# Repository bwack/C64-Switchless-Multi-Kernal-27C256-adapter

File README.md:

[![Badge License]][License]

<br>

![Logo]

<br>

<div align = center>

***A C64 + Disk Drives Switch-less Multi*** <br>
***Kernel ROM Adapter / Switcher***

<br>

---

[![Button Playlist]][Playlist]   
[![Button OSHPark]][OSHPark]   
[![Button Forum]][Forum]

[![Button Usage]][Usage]  
[![Button Develop]][Develop]  
[![Button Changelog]][Changelog]

---

<br>
<br>

<br>

## Supported Devices

![C64]  ![C64C]  ![1541]  ![1541C]  ![1541-II] 

<br>

</div>
  
<br>

## Boards

### Long

The  `longboard`  is designed for <br>
the  <kbd> C64 </kbd>  **+**  <kbd> 1541 </kbd>  **/**  <kbd> 1541Late </kbd>

<br>

### Short

The  `shortboard`  is designed for <br>
the  <kbd> C64C </kbd>  **+**  <kbd> 1541C </kbd>  **/**  <kbd> 1541-II </kbd>

<br>

### Note

*The innards of  `C64`  /  `C64C`  and  `1541`  /  `1541C`* <br>
*are often mixed together, and you must check their* <br>
*cases to be sure which boards they have.*

<br>
<br>

## Acknowledgment

### Based On   [<kbd> Sven Petersen </kbd>][Petersen]

*[C64 Kernal Adaptor Switch Shortboard]*

### Old Version   [<kbd> DiscoHR </kbd>][DiscoHR]

*[C64C C128 Multikernal Adapter]*

*It is possible to reused the original LED / Cable assembly.*

### Idea From   [<kbd> Tebl </kbd>][DiscoHR]

*[C64 Kernal Switcher]*

<br>

<!----------------------------------------------------------------------------->

[Playlist]: https://www.youtube.com/playlist?list=PLtQOf_JULmrQTB7486X5pXG1Aaxbl_RdE
[OSHPark]: https://oshpark.com/profiles/bwack 'Order The Board'
[Forum]: http://www.lemon64.com/forum/viewtopic.php?p=747333 'Lemon64 Forum Post'

[Changelog]: Documentation/Changelog.md
[Develop]: Documentation/Develop.md
[License]: LICENSE
[Usage]: Documentation/Usage.md
[Logo]: User%20Guide/media/SKS64-Logos-Ver2.png

[Badge License]: https://img.shields.io/badge/Open_Hardware-1.2-292961?style=for-the-badge

<!--------------------------------{ Devices }---------------------------------->

[1541-II]: https://img.shields.io/badge/１５４１－ＩＩ-d7cdbb?style=flat
[1541C]: https://img.shields.io/badge/１５４１Ｃ-d7cdbb?style=flat
[1541]: https://img.shields.io/badge/１５４１-d7cdbb?style=flat
[C64C]: https://img.shields.io/badge/Ｃ６４Ｃ-d7cdbb?style=flat
[C64]: https://img.shields.io/badge/Ｃ６４-d7cdbb?style=flat

<!----------------------------{ Acknowledgment }------------------------------->

[C64 Kernal Adaptor Switch Shortboard]: https://github.com/svenpetersen1965/C64-Kernal-Adaptor-Switch-short-board-
[C64C C128 Multikernal Adapter]: https://github.com/discoHR/C64C-C128-multikernal-adapter
[C64 Kernal Switcher]: https://github.com/tebl/C64-Kernal-Switcher

[Petersen]: https://github.com/svenpetersen1965
[DiscoHR]: https://github.com/discoHR
[Tebl]: https://github.com/tebl

<!--------------------------------{ Buttons }---------------------------------->

[Button Changelog]: https://img.shields.io/badge/Changelog-19abdd?style=for-the-badge&logoColor=white&logo=AzureArtifacts
[Button Playlist]: https://img.shields.io/badge/Playlist-FF0000?style=for-the-badge&logoColor=white&logo=Youtube
[Button Develop]: https://img.shields.io/badge/Develop-00979D?style=for-the-badge&logoColor=white&logo=Arduino
[Button OSHPark]: https://img.shields.io/badge/OSHPark-752c8d?style=for-the-badge&logoColor=white&logo=Houzz
[Button Usage]: https://img.shields.io/badge/Usage-ED145B?style=for-the-badge&logoColor=white&logo=AppleArcade
[Button Forum]: https://img.shields.io/badge/Forum-5287B8?style=for-the-badge&logoColor=white&logo=AskUbuntu

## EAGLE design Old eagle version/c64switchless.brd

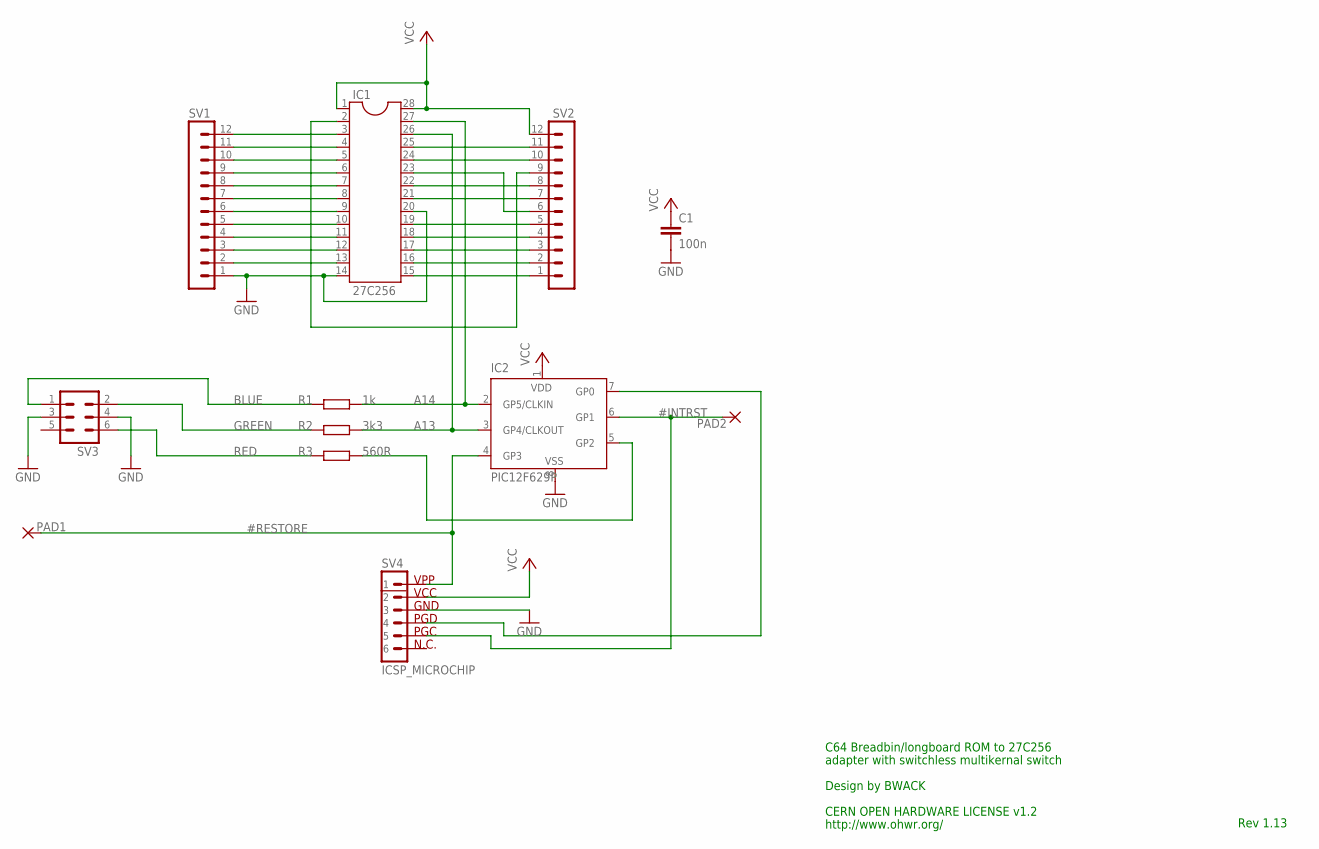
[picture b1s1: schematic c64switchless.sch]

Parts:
C1: 100n; C025-024X044
IC1: 27C256; DIL28SPECIAL
IC2: PIC12F629P; DIL8
PAD1, PAD2: WIREPAD1,6/0,9; 1,6/0,9
R1: 1k; 0207/10
R2: 3k3; 0207/10
R3: 560R; 0207/10
SV1, SV2: MA12-1ROUND
SV3: MA03-2
SV4: ICSP_MICROCHIP

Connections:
#INTRST: IC2.6 (GP1), PAD2.1, SV4.5
#RESTORE: IC2.4 (GP3), PAD1.1, SV4.1
A13: IC1.26, IC2.3 (GP4/CLKOUT), R2.2
A14: IC1.27, IC2.2 (GP5/CLKIN), R1.2
BLUE: R1.1, SV3.1
GND: C1.2, IC1.14, IC1.20, IC2.8 (VSS), SV1.1, SV3.3, SV3.4, SV4.3
GREEN: R2.1, SV3.2
unnamed: IC2.7 (GP0), SV4.4
unnamed: IC1.13, SV1.2
unnamed: IC1.12, SV1.3
unnamed: IC1.11, SV1.4
unnamed: IC1.10, SV1.5
unnamed: IC1.9, SV1.6
unnamed: IC1.8, SV1.7
unnamed: IC1.7, SV1.8
unnamed: IC1.6, SV1.9
unnamed: IC1.5, SV1.10
unnamed: IC1.4, SV1.11
unnamed: IC1.3, SV1.12
unnamed: IC1.15, SV2.1
unnamed: IC1.16, SV2.2
unnamed: IC1.17, SV2.3
unnamed: IC1.18, SV2.4
unnamed: IC1.19, SV2.5
unnamed: IC1.21, SV2.7
unnamed: IC1.22, SV2.8
unnamed: IC1.24, SV2.10
unnamed: IC1.25, SV2.11
unnamed: IC2.5 (GP2), R3.2
unnamed: IC1.23, SV2.6
unnamed: IC1.2, SV2.9
RED: R3.1, SV3.6
VCC: C1.1, IC1.1, IC1.28, IC2.1 (VDD), SV2.12, SV4.2

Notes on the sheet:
C64 Breadbin/longboard ROM to 27C256
adapter with switchless multikernal switch
Design by BWACK
Rev 1.13
http://www.ohwr.org/
CERN OPEN HARDWARE LICENSE v1.2

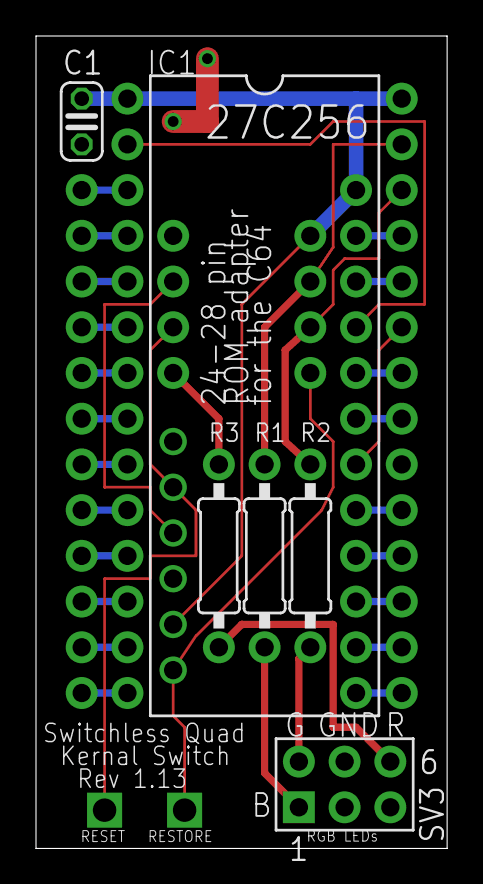
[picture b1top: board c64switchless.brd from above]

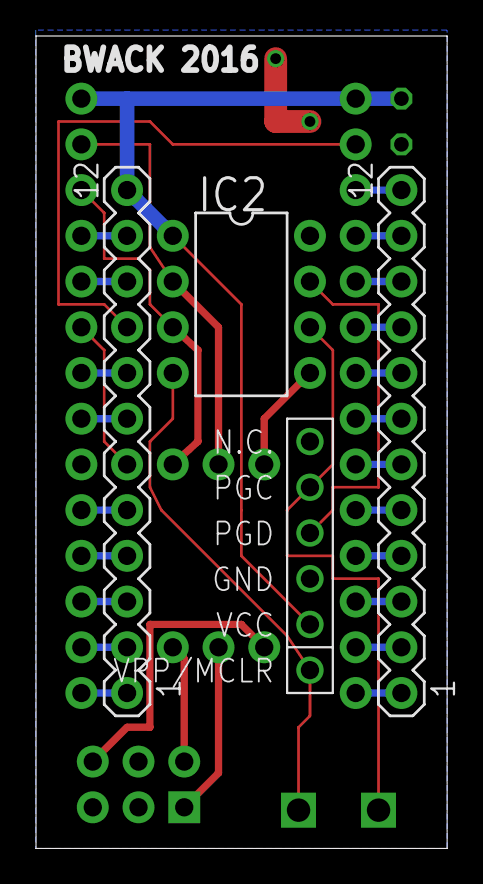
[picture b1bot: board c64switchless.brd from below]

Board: 2 copper layers, 22.8 x 45.1 mm, 12 parts (4 on the bottom side), 33 nets.

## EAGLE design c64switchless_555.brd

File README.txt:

README.txt (2016-09-28)

C64 Switchless Multi Kernel Switch
- 27C256 rom adapter for C64's with long motherboard

Designed by BWACK.
CERN OPEN HARDWARE LICENSE v1.2
http://www.ohwr.org/

The Eagle CAD files are available on GitHub:
https://github.com/bwack/C64-Switchless-Multi-Kernal-27C256-adapter

All text above must be included in any redistribution

Note: longboards (not 250469) and shortboards (250469) are sometimes mixed up with C64C and C64, so you must open the machine up to be sure you've got the longboard.

Project links:
  lemon64:  http://www.lemon64.com/forum/viewtopic.php?p=747333
  playlist: https://www.youtube.com/watch?v=oGaI8yLwjh4&list=PLtQOf_JULmrQTB7486X5pXG1Aaxbl_RdE
  OSH Park: https://oshpark.com/profiles/bwack
  Github:   https://github.com/bwack/C64-Switchless-Multi-Kernal-27C256-adapter

Changelog:
Rev 1.13 (2016-09-28): Moved IC2 down to clear space for the socket in the c64.
                       Changes to the silk screen.
Rev 1.12 (2016-09-18): Increased padd and hole sizes. Removed ground fill from top layer.
         (2016-09-17): Added CERN OHL v1.2 License.
Rev 1.11 (2016-09-10): RGB Led header following RGB led pinout (Blue-Green-GND-Red).
                       Editted silkscreen.
Rev 1.1  (2016-09-08): sch+brd. Swapped signals #RESTORE and RED_LED, because GP3 on the
                       MCU is input only.
Note: The schematic revision follows the board revision number.

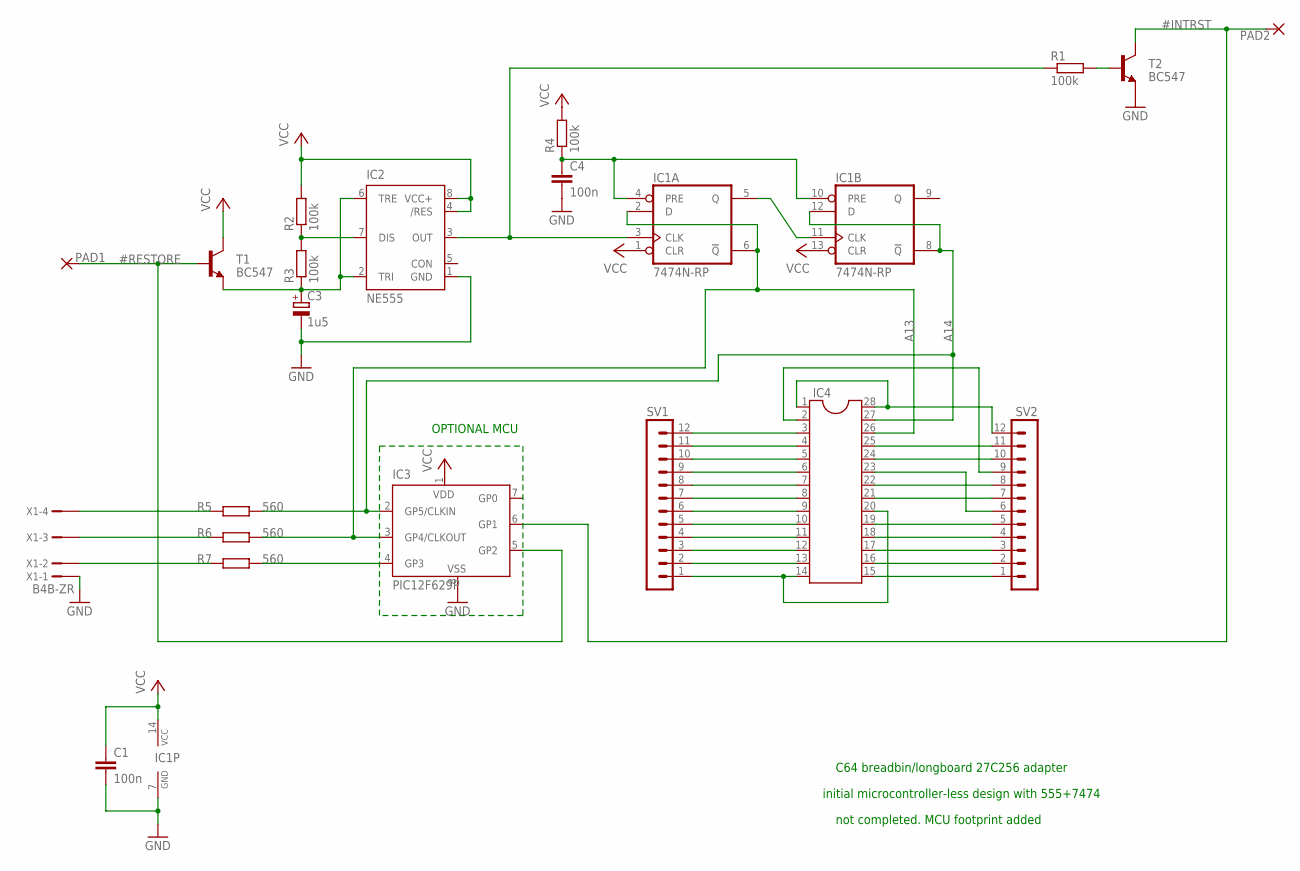
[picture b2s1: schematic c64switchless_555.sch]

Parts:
C1, C4: 100n; C050-030X075
C3: 1u5; E2,5-6
IC1: 7474N-RP; DIL14-ROUNDPADS
IC2: NE555; DIL-08
IC3: PIC12F629P; DIL8
IC4: DIL28ROUND; DIL28SPECIAL
PAD1, PAD2: WIREPAD2,54/1,0; 2,54/1,0
R1, R2, R3, R4: 100k; 0204/7
R5, R6, R7: 560; 0204/7
SV1, SV2: MA12-1ROUND
T1, T2: BC547; TO92
X1: B4B-ZR

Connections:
#INTRST: IC3.6 (GP1), PAD2.1, T2.3 (C)
#RESTORE: IC3.5 (GP2), PAD1.1, T1.2 (B)
A13: IC1.2 (D), IC1.6 (!Q), IC3.3 (GP4/CLKOUT), IC4.26, R6.2
A14: IC1.8 (!Q), IC1.12 (D), IC3.2 (GP5/CLKIN), IC4.27, R5.2
GND: C1.2, C3.-, C4.2, IC1.7 (GND), IC2.1 (GND), IC3.8 (VSS), T2.1 (E), X1.1
unnamed: IC4.14, IC4.20, SV1.1
unnamed: IC4.13, SV1.2
unnamed: IC4.12, SV1.3
unnamed: IC4.11, SV1.4
unnamed: IC4.10, SV1.5
unnamed: IC4.9, SV1.6
unnamed: IC4.8, SV1.7
unnamed: IC4.7, SV1.8
unnamed: IC4.6, SV1.9
unnamed: IC4.5, SV1.10
unnamed: IC4.4, SV1.11
unnamed: IC4.3, SV1.12
unnamed: IC4.15, SV2.1
unnamed: IC4.16, SV2.2
unnamed: IC4.17, SV2.3
unnamed: IC4.18, SV2.4
unnamed: IC4.19, SV2.5
unnamed: IC4.21, SV2.7
unnamed: IC4.22, SV2.8
unnamed: IC4.24, SV2.10
unnamed: IC4.25, SV2.11
unnamed: IC4.1, IC4.28, SV2.12
unnamed: IC4.23, SV2.6
unnamed: IC4.2, SV2.9
unnamed: R1.2, T2.2 (B)
unnamed: C3.+, IC2.2 (TRI), IC2.6 (TRE), R3.1, T1.1 (E)
unnamed: IC2.7 (DIS), R2.1, R3.2
unnamed: IC3.4 (GP3), R7.2
unnamed: IC1.5 (Q), IC1.11 (CLK)
unnamed: C4.1, IC1.4 (PRE), IC1.10 (PRE), R4.1
unnamed: R5.1, X1.4
unnamed: R6.1, X1.3
unnamed: R7.1, X1.2
unnamed: IC1.3 (CLK), IC2.3 (OUT), R1.1
VCC: C1.1, IC1.1 (CLR), IC1.13 (CLR), IC1.14 (VCC), IC2.4 (/RES), IC2.8 (VCC+), IC3.1 (VDD), R2.2, R4.2, T1.3 (C)

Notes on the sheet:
C64 breadbin/longboard 27C256 adapter
initial microcontroller-less design with 555+7474
not completed. MCU footprint added
OPTIONAL MCU

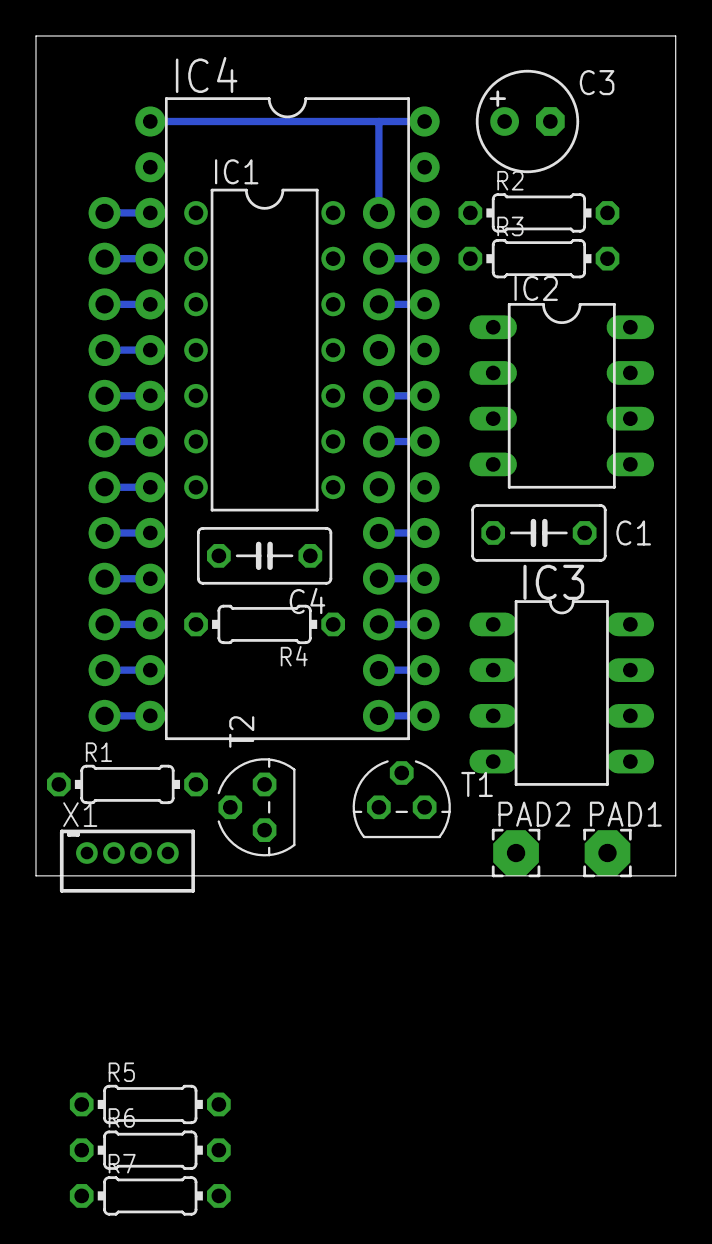
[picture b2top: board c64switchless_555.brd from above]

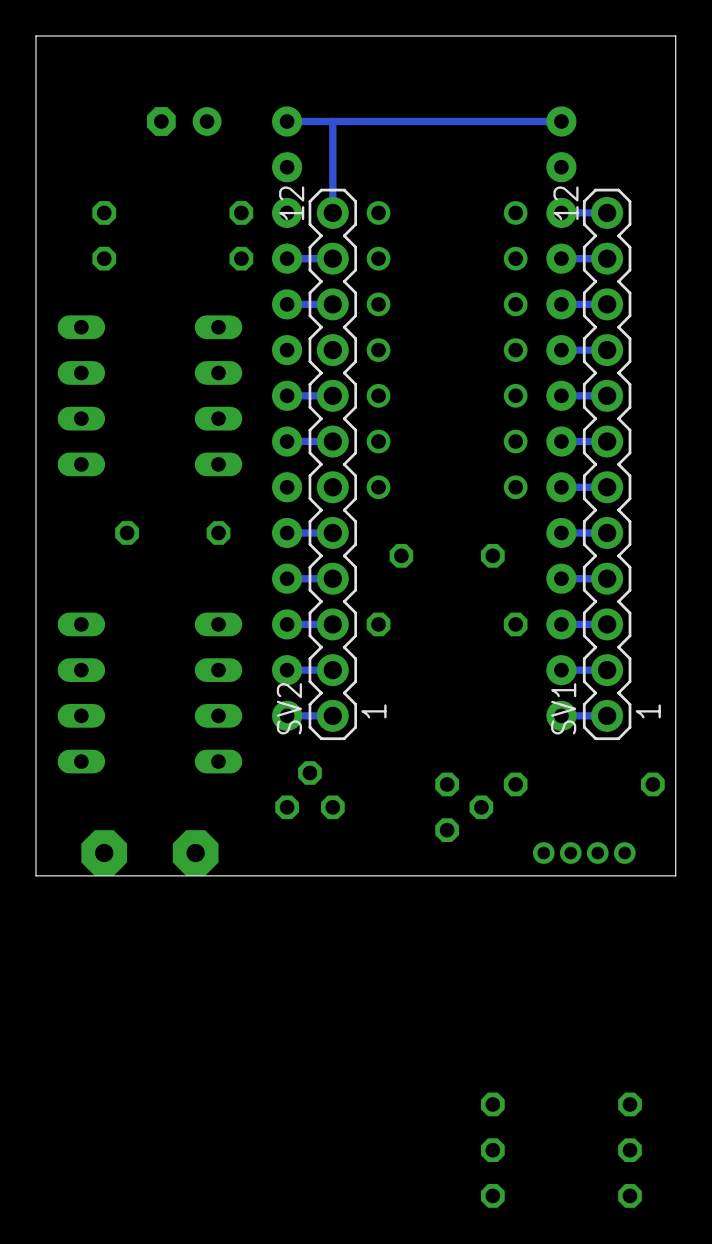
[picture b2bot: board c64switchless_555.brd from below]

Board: 2 copper layers, 35.5 x 46.7 mm, 21 parts (2 on the bottom side), 40 nets.

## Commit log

2016-08-20 :boom::camel: Added .gitattributes
2016-08-20 first commit
    my first commit
2016-08-20 PDF file added
    Note that this 555 based design is not completed.
2016-08-20 Optional MCU
    The MCU is optional in the 555 design. I added the footprint because
    space was available. Not finished.
2016-08-22 555 based: updated R2,R3. Added revision.
2016-08-22 Revision + silkscreen text
2016-09-08 swapped LED and RESTORE on GP2 and GP3
    GP3 is the fekken input only pin
2016-09-08 Rev 1.1 of the microcontroller files
2016-09-09 We need a README file
2016-09-09 added instant select-mode from reset button (discobranch)
2016-09-10 Sch+Layout changed to match RGB LEDs pinout
    See readme.txt
2016-09-10 Rev 1.11 Silkscreen, RGB LED
2016-09-10 silkscreen was on wrong layer - move 555 version
2016-09-10 Bill of materials
2016-09-16 disable eeprom at debug time
2016-09-16 removed kernal=0 and using switch-case block
2016-09-17 gitignore and hex file.
2016-09-17 hexfile
2016-09-17 project file
2016-09-17 LICENSE
2016-09-17 updated with license
2016-09-18 hole sizes
2016-09-19 mikroC config file
2016-09-28 Rev 1.13
    Moved IC2 to clear space for the socket in the C64.
2016-10-22 putting the mcu to sleep
2016-11-18 the hex-file i forgot to include
2017-10-02 Added support for PIC12F675
2017-10-08 The very early planning for the User Guide
2017-10-09 The beginning of a User Guide
2017-11-10 documentation still at a very early stage
2017-11-19 Documented the LED assembly and overview.
    PDF is old.
2018-05-06 Minor change.
2019-05-16 Added assembly instructions in the manual
2019-05-16 resistor values
2019-06-22 schematics and layout in user guide
2019-06-22 README rename
2019-06-22 Rename README to README.md
2019-06-23 Link to tebl's repository
2019-07-14 V1.20
2019-07-14 3d images
2019-07-15 User Guide
    not finished
2019-07-15 Via locations on longboard motherboards
2019-07-15 typo
2019-07-17 firmware updates: use eprom, exromreset, opencollector
    opencollector-ish means set reset and exrom as input when inactive.
2019-07-17 User Guide
2019-07-18 Update readme.md, shortboard version
2019-07-18 Preparing for shortboard version
2019-07-18 User Guide. Soldering instructions
2019-07-18 Update SKS64_SKETCH.ino
    still a bit buggy
2019-07-19 Firmware: Setup menu, motherboard and no. banks stored on eprom, small bugfixes
    Only need one firmware for all the possible usage types
    longboard, shortboard, 4 banks, 8 banks.
2019-07-20 User Guide update, the firmware.
2019-07-20 shortboard version not tested
2019-07-20 Don't rotate setup when entering setup menu
2019-07-21 Readme, 250469 wiring, user guide
2019-07-22 removed delays in setup, sleepmode when idle,
2019-07-23 longboard pcb version, 8 bank support
2019-07-24 shortboard version schematics added to user guide
2019-07-24 RED turned on after EXROM reset (flashcounter not zero)
2019-08-12 Updated BOM shortboard in User Guide. Added mouserproject link
2019-08-13 User Guide updated. 8 kernals in v1.21 confirmed working.
2020-04-13 Added the old PIC12F hex files again
2021-01-06 Set EXROM to input on startup instead of output - otherwise EXROM is held high until first reboot
2021-05-02 Firmware 1.2
2021-05-03 Removed led flashing delay at start of program. The flashing caused C64C to not warm start.
2021-05-03 Updated User Guide. Make it clearer to select fusebits.
2021-07-27 1.4 fixed: A15 always 0 at cold boot in 8 banks longboard mode
2021-08-10 1541C support in firmware and SKS64 shortboard pcb version
2021-08-10 firmware: removed startup delay (1s) causing startup issues
2021-08-10 Documentation update includes 1541
2021-10-19 build makefiles for making the four firmware variants
2022-04-03 The arduino code ported to atmega328p (arduino uno)
2022-05-28 Moved Changelog Into Dedicated File
2022-05-28 Added Quicklink
2022-05-28 Added More Quicklinks
2022-05-28 Added License Badge
2022-05-28 Adjusted Spacing
2022-05-28 Formatted Changelog
2022-05-28 Adjusted Formatting
2022-05-29 Formatted Supported Devices
2022-05-29 Moved Usage & Develop Into Dedicated Files
2022-05-29 Moved Usage & ...
2022-05-29 Formatted Acknowledgment
2022-05-29 Formatted Boards Section
2022-05-29 Formatted Develop
2022-05-29 Formatted Usage
